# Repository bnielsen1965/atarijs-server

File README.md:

# atarijs-server

A NodeJS based server used to emulate Atari floppy drives on the SIO interface and
provide a web based user interface for loading of floppy disk images into emulated
drives.

**WARNING:** Always make backup copies of your floppy disk images. When clicking
on the save button on a drive control the disk image in memory will overwrite the
image file on your hard drive.

# Requirements

What will you need?
- Host platform to run the server and connect to an Atari (developed and tested on linux).
- [NodeJS](https://nodejs.org) engine installed on the host platform.
- RS232 to Atari SIO adapter. See the [hardware](#hardware) below for a possible solution.
- ATR floppy images. A set of floppy disk images will be needed for the emulation.

# Install

Copy the project from github, then use *npm install* in the project directory to
load all the dependencies.

```shell
git clone https://github.com/bnielsen1965/atarijs-server.git
cd atarijs-server
npm install
```

Next edit the config.js file and set the *SerialDevice* value to your RS232 device
that is connected to the Atari SIO interface.

Copy your floppy disk image files into the */atarijs-server/public/images* directory
where they will be hosted by the server.

And finally use node to start the atarijs-server server.
> node index.js

You can now open up the web interface in a web browser by entering the address and
port to the host server. I.E. if the atarijs server is running on the same system
as the web browser then enter [http://localhost:8080/](http://localhost:8080/) in
the web browser, or if you atarijs server is on a remote host then use the ip address
of the host, I.E. [http://192.168.0.18:8080](http://192.168.0.18:8080).

# User Interface

The user interface is a simple web page with a list of emulated floppy drives
on the left and a list of floppy disk image files on the right.

Drag a floppy disk image from the list on the right to input field on an
emulated drive on the left and the server will load that image into the
emulated drive.

If additional image files are added to the */atarijs-server/public/images*
folder then the list of floppy disk images can be refreshed by clicking the
refresh icon in the upper right corner.

If changes are made to the disk in an emulated drive those changes can be
saved back to the image file by clicking on the *save disk* icon in the
emulated drive controls.

The image in an emulated drive can be ejected by clicking on the *eject* icon
on the drives controls.

**WARNING:** If changes are made to a floppy and it is ejected before saving
then the changes will be lost.

# Hardware

The atarijs-server should theoretically work with any RS232 to Atari SIO
adapter. The following is the hardware solution that was used during
development of atarijs-server.

**WARNING:** Use this hardware design at your own risk. The RS232 standard
specifies voltages that may range +/- 15VDC and depending on the RS232
hardware used you could damage your Atari computer or peripherals.

This circuit is used with the CableCreation USB to RS232 Adapter (FTDI
Chipset). A 74HC14 hex inverting Schmitt trigger is used to convert between
the 0 to 5 VDC signals on the Atari SIO and the RS232 voltages from the
RS232 adapter.

The +5 VDC Ready signal from the Atari SIO is used to power the 74HC14 chip
and three of the hex inverter Schmitt trigger gates are used to connect the
Atar SIO Data Out to RS232 RxD, SIO Data In to RS232 TxD, and SIO Command
to RS232 CTS. The result is a compact PCB...

An FTDI based USB to RS-232 cable was used with this 74HC14 based SIO to RS-232
adapter for testing. The signal voltages out of the FTDI based cable were on the
low end of the RS-232 specification so there may not be any risk of over voltage
damage.

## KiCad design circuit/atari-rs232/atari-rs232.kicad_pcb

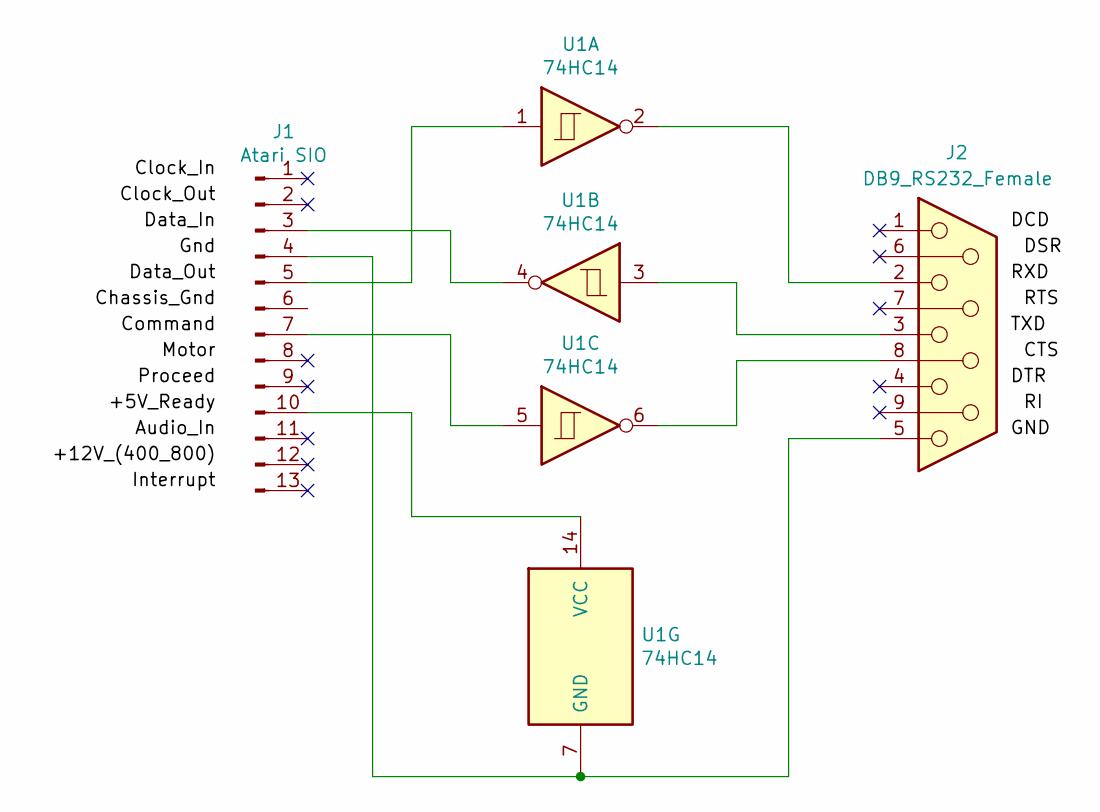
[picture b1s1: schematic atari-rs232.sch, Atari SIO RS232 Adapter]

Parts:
J1: Atari SIO; PinHeader_1x13_P2.54mm_Vertical
J2: DB9_RS232_Female; DSUB-9_Female_Horizontal_P2.77x2.54mm_EdgePinOffset9.40mm
U1: 74HC14; DIP-14_W7.62mm

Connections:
unnamed: J1.3, U1.4
unnamed: J1.4, J2.5, U1.7 (GND)
unnamed: J1.5, U1.1
unnamed: J1.7, U1.5
unnamed: J1.10, U1.14 (VCC)
unnamed: J2.2, U1.2
unnamed: J2.3, U1.3
unnamed: J2.8, U1.6

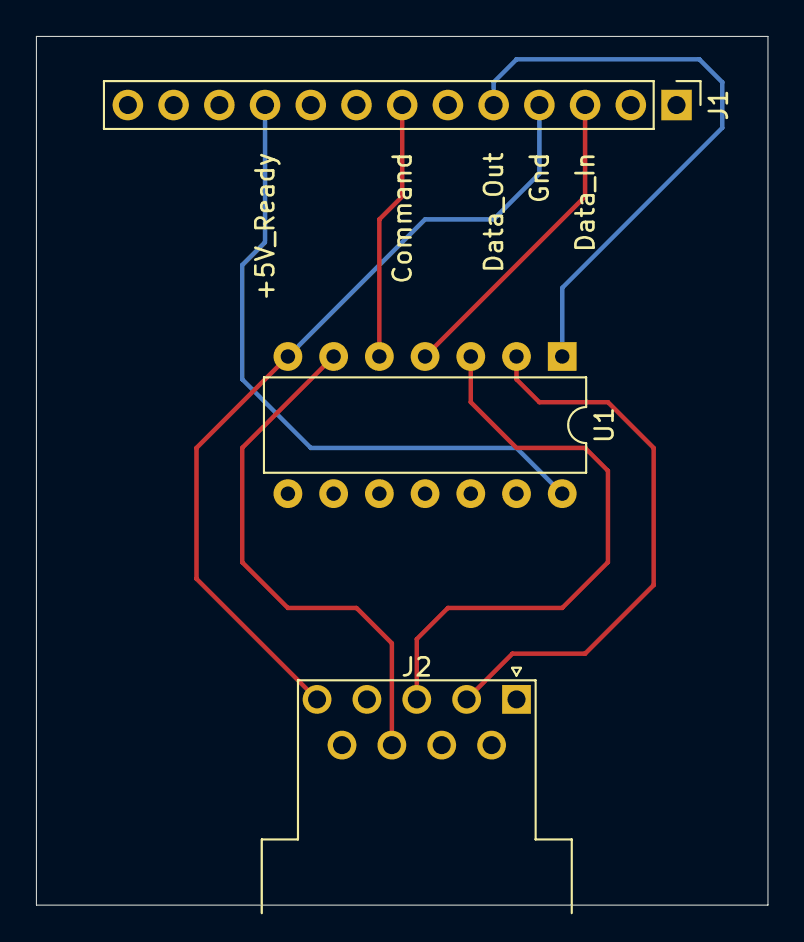
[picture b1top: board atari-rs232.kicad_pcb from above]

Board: 2 copper layers, 40.6 x 48.3 mm, 3 parts (0 on the bottom side), 8 nets.

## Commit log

2016-09-16 Initial commit.
2016-09-18 Start web pages for user interface.
2016-09-18 Added get status method and more detail to each drive.
2016-09-19 Added slots to temporarily park images. Added ability to import, export, and save images.
2016-09-19 Added the README.md
2016-09-20 Adding more detail to the README.md.
2016-09-20 Adding detail to UI.
2016-09-25 Added image eject from drive. Fixed z-indexing of draggable drive image.
2016-09-25 Add ability to change image filename.
2021-03-29 Rewrite to some dependencies. Added new hardware design.
2021-04-08 Add picture of a finished cable.
